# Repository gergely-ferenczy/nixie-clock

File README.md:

4 digit IN-8-2 Nixie clock with schematic and code implementation for a TM4C1231 microcontroller.

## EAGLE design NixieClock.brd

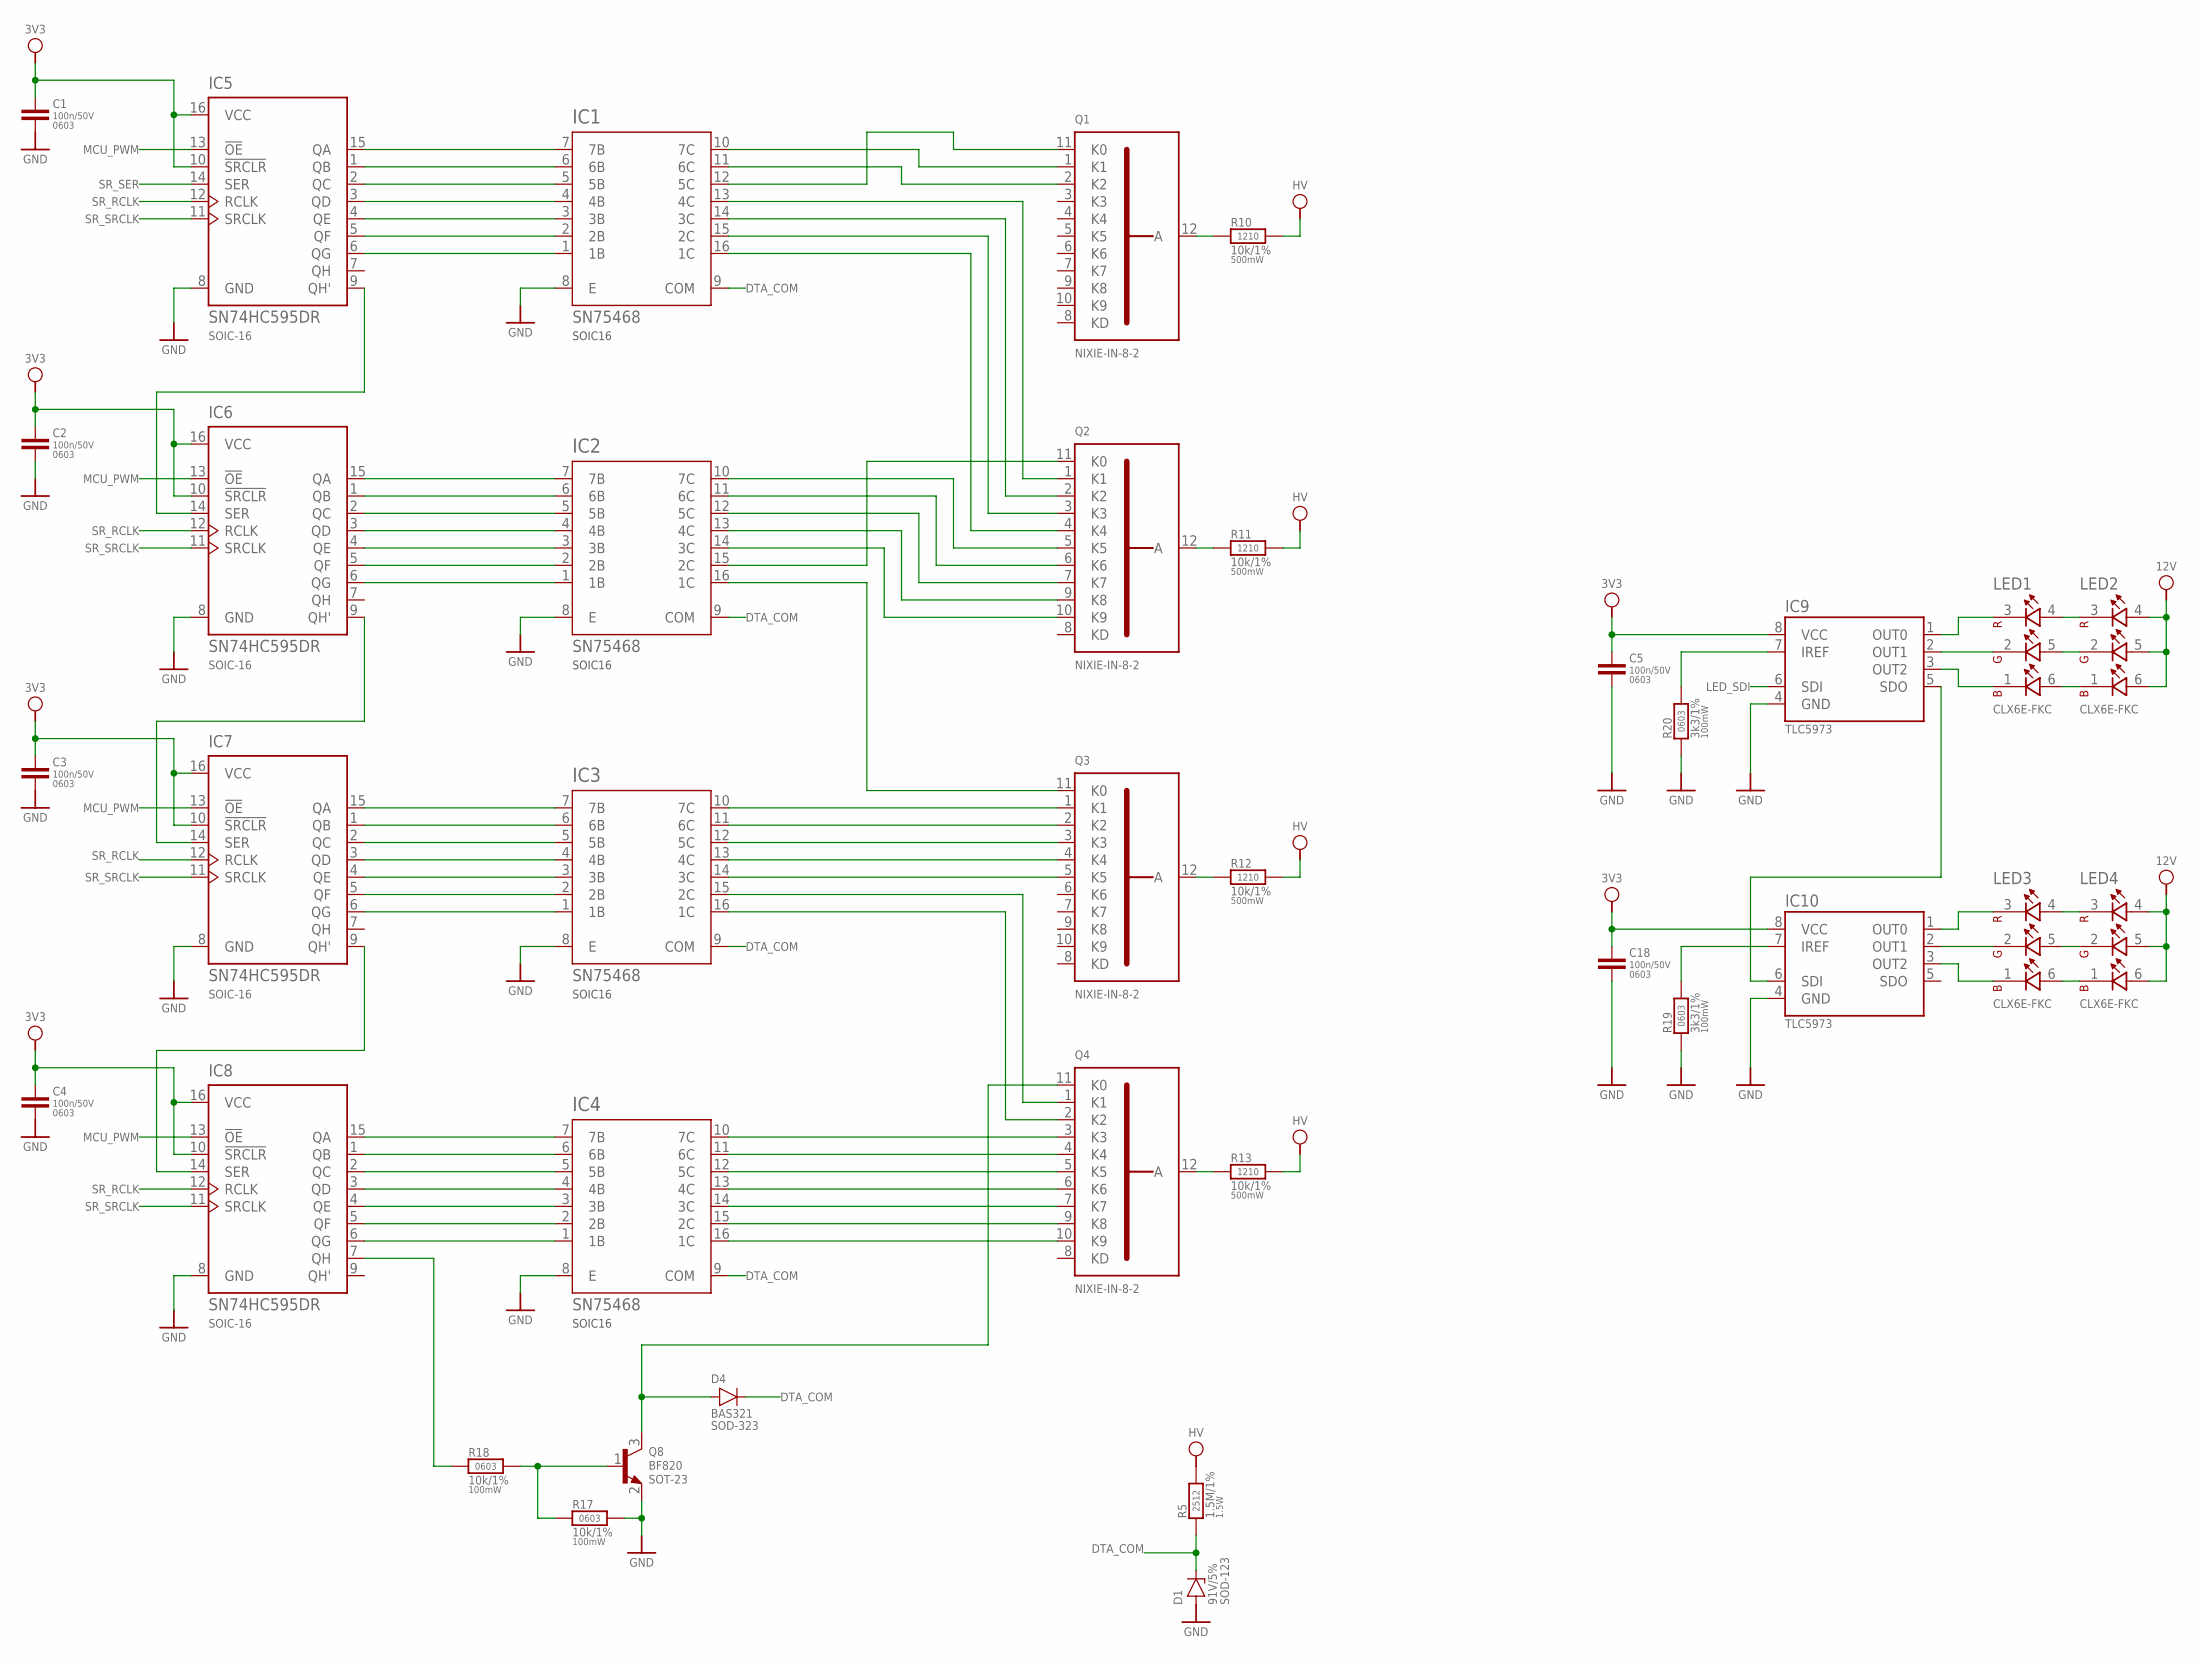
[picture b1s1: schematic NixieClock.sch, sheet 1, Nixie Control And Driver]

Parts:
C1, C2, C3, C4, C5, C18: 100n/50V; CAPC1608X80N
D1: 91V/5%; SOD3716X135N
D4: BAS321; SOD2512X110N
IC1, IC2, IC3, IC4: SN75468; SOIC127P600X175-16N
IC5, IC6, IC7, IC8: SN74HC595DR; SOIC127P600X175-16N
IC9, IC10: TLC5973; SOIC127P600X175-8N
LED1, LED2, LED3, LED4: CLX6E-FKC
Q1, Q2, Q3, Q4: NIXIE-IN-8-2
Q8: BF820; SOT95P230X110-3N
R5: 1.5M/1%; RESC6331X65N
R10, R11, R12, R13: 10k/1%; RESC3225X60N
R17, R18: 10k/1%; RESC1608X50N
R19, R20: 3k3/1%; RESC1608X50N

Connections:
3V3: C1.1, C2.1, C3.1, C4.1, C5.1, C18.1, IC5.10 (!SRCLR), IC5.16 (VCC), IC6.10 (!SRCLR), IC6.16 (VCC), IC7.10 (!SRCLR), IC7.16 (VCC), IC8.10 (!SRCLR), IC8.16 (VCC), IC9.8 (VCC), IC10.8 (VCC); also elsewhere on the board
12V: LED2.4 (ARED), LED2.5 (AGREEN), LED2.6 (ABLUE), LED4.4 (ARED), LED4.5 (AGREEN), LED4.6 (ABLUE); also elsewhere on the board
DTA_COM: D1.1, D4.1, IC1.9 (COM), IC2.9 (COM), IC3.9 (COM), IC4.9 (COM), R5.1
GND: C1.2, C2.2, C3.2, C4.2, C5.2, C18.2, D1.2, IC1.8 (E), IC2.8 (E), IC3.8 (E), IC4.8 (E), IC5.8 (GND), IC6.8 (GND), IC7.8 (GND), IC8.8 (GND), IC9.4 (GND), IC10.4 (GND), Q8.2 (E), R17.2, R19.1, R20.1; also elsewhere on the board
HV: R5.2, R10.2, R11.2, R12.2, R13.2; also elsewhere on the board
LED_SDI: IC9.6 (SDI); also elsewhere on the board
MCU_PWM: IC5.13 (!OE), IC6.13 (!OE), IC7.13 (!OE), IC8.13 (!OE); also elsewhere on the board
unnamed: IC1.7 (7B), IC5.15 (QA)
unnamed: IC1.6 (6B), IC5.1 (QB)
unnamed: IC1.5 (5B), IC5.2 (QC)
unnamed: IC1.4 (4B), IC5.3 (QD)
unnamed: IC1.3 (3B), IC5.4 (QE)
unnamed: IC1.2 (2B), IC5.5 (QF)
unnamed: IC1.1 (1B), IC5.6 (QG)
unnamed: IC5.9 (QH'), IC6.14 (SER)
unnamed: IC1.10 (7C), Q1.1 (K1)
unnamed: IC1.11 (6C), Q1.2 (K2)
unnamed: IC1.12 (5C), Q1.11 (K0)
unnamed: IC1.13 (4C), Q2.1 (K1)
unnamed: IC1.14 (3C), Q2.2 (K2)
unnamed: IC1.15 (2C), Q2.3 (K3)
unnamed: IC1.16 (1C), Q2.4 (K4)
unnamed: IC6.9 (QH'), IC7.14 (SER)
unnamed: IC2.10 (7C), Q2.5 (K5)
unnamed: IC2.11 (6C), Q2.6 (K6)
unnamed: IC2.12 (5C), Q2.7 (K7)
unnamed: IC2.13 (4C), Q2.9 (K8)
unnamed: IC2.14 (3C), Q2.10 (K9)
unnamed: IC2.15 (2C), Q2.11 (K0)
unnamed: IC2.7 (7B), IC6.15 (QA)
unnamed: IC7.9 (QH'), IC8.14 (SER)
unnamed: IC2.6 (6B), IC6.1 (QB)
unnamed: IC2.5 (5B), IC6.2 (QC)
unnamed: IC2.4 (4B), IC6.3 (QD)
unnamed: IC2.3 (3B), IC6.4 (QE)
unnamed: IC2.2 (2B), IC6.5 (QF)
unnamed: IC2.1 (1B), IC6.6 (QG)
unnamed: IC3.7 (7B), IC7.15 (QA)
unnamed: IC3.6 (6B), IC7.1 (QB)
unnamed: IC3.5 (5B), IC7.2 (QC)
unnamed: IC3.4 (4B), IC7.3 (QD)
unnamed: IC3.3 (3B), IC7.4 (QE)
unnamed: IC3.2 (2B), IC7.5 (QF)
unnamed: IC3.1 (1B), IC7.6 (QG)
unnamed: IC8.7 (QH), R18.1
unnamed: IC9.1 (OUT0), LED1.3 (CRED)
unnamed: IC9.3 (OUT2), LED1.1 (CBLUE)
unnamed: IC9.2 (OUT1), LED1.2 (CGREEN)
unnamed: IC4.11 (6C), Q4.4 (K4)
unnamed: IC10.1 (OUT0), LED3.3 (CRED)
unnamed: IC4.7 (7B), IC8.15 (QA)
unnamed: IC4.6 (6B), IC8.1 (QB)
unnamed: IC4.5 (5B), IC8.2 (QC)
unnamed: IC4.4 (4B), IC8.3 (QD)
unnamed: IC4.3 (3B), IC8.4 (QE)
unnamed: IC4.2 (2B), IC8.5 (QF)
unnamed: IC4.1 (1B), IC8.6 (QG)
unnamed: IC2.16 (1C), Q3.11 (K0)
unnamed: IC3.14 (3C), Q3.5 (K5)
unnamed: IC3.13 (4C), Q3.4 (K4)
unnamed: IC3.12 (5C), Q3.3 (K3)
unnamed: Q1.12 (A), R10.1
unnamed: IC3.11 (6C), Q3.2 (K2)
unnamed: IC3.10 (7C), Q3.1 (K1)
unnamed: IC3.15 (2C), Q4.1 (K1)
unnamed: IC3.16 (1C), Q4.2 (K2)
unnamed: IC4.10 (7C), Q4.3 (K3)
unnamed: IC4.12 (5C), Q4.5 (K5)
unnamed: IC4.13 (4C), Q4.6 (K6)
unnamed: IC4.14 (3C), Q4.7 (K7)
unnamed: Q8.1 (B), R17.1, R18.2
unnamed: IC4.15 (2C), Q4.9 (K8)
unnamed: IC4.16 (1C), Q4.10 (K9)
unnamed: D4.2, Q4.11 (K0), Q8.3 (C)
unnamed: IC10.2 (OUT1), LED3.2 (CGREEN)
unnamed: IC10.3 (OUT2), LED3.1 (CBLUE)
unnamed: Q2.12 (A), R11.1
unnamed: Q3.12 (A), R12.1
unnamed: Q4.12 (A), R13.1
unnamed: LED3.4 (ARED), LED4.3 (CRED)
unnamed: LED3.5 (AGREEN), LED4.2 (CGREEN)
unnamed: LED3.6 (ABLUE), LED4.1 (CBLUE)
unnamed: LED1.4 (ARED), LED2.3 (CRED)
unnamed: LED1.5 (AGREEN), LED2.2 (CGREEN)
unnamed: LED1.6 (ABLUE), LED2.1 (CBLUE)
unnamed: IC9.7 (IREF), R20.2
unnamed: IC10.7 (IREF), R19.2
unnamed: IC9.5 (SDO), IC10.6 (SDI)
SR_RCLK: IC5.12 (RCLK), IC6.12 (RCLK), IC7.12 (RCLK), IC8.12 (RCLK); also elsewhere on the board
SR_SER: IC5.14 (SER); also elsewhere on the board
SR_SRCLK: IC5.11 (SRCLK), IC6.11 (SRCLK), IC7.11 (SRCLK), IC8.11 (SRCLK); also elsewhere on the board

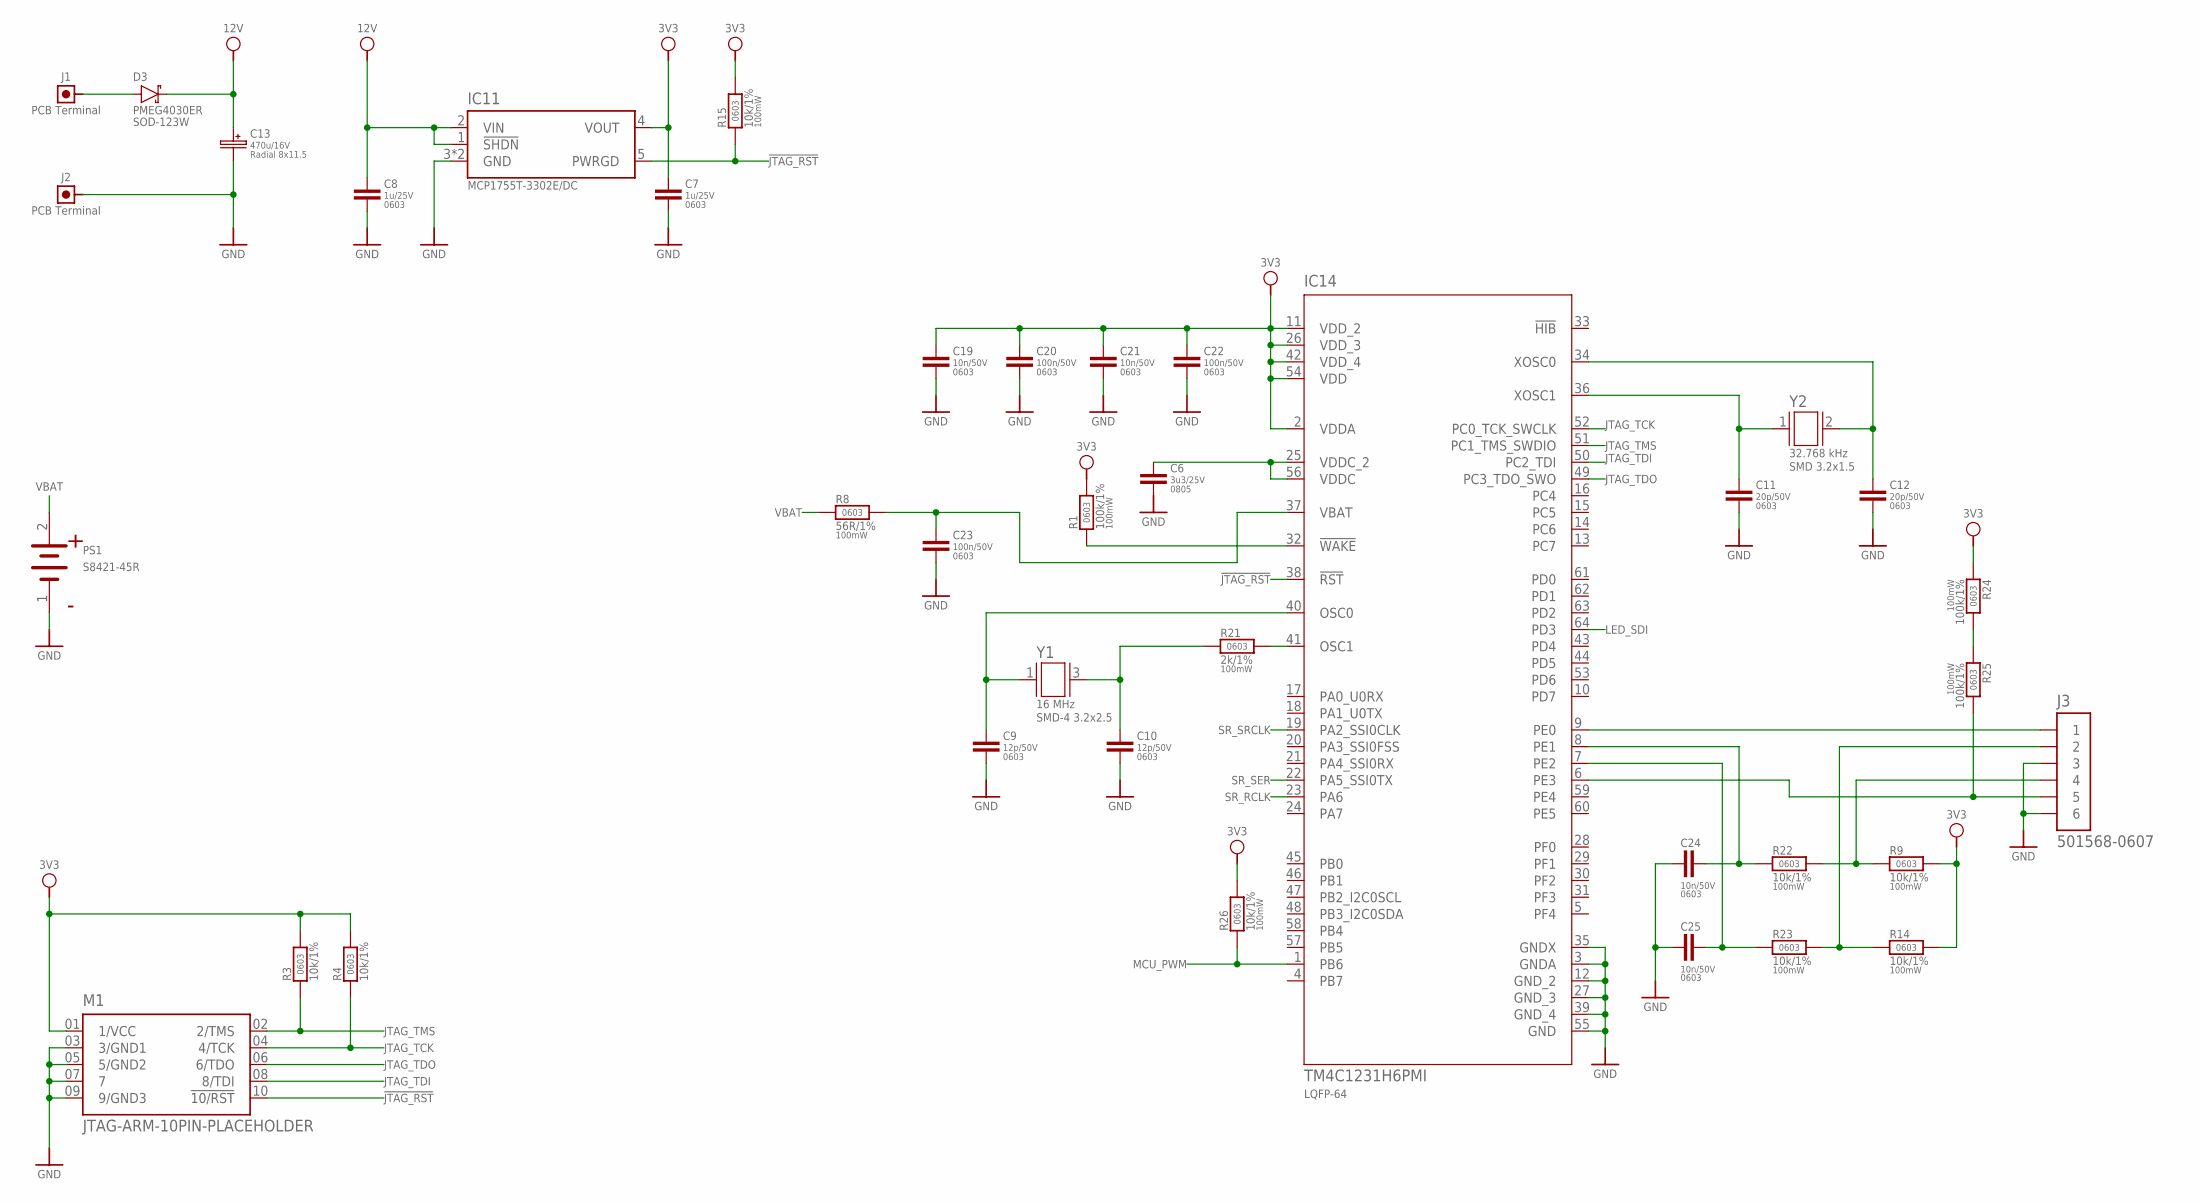
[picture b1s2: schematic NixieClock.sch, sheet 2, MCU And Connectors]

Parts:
C6: 3u3/25V; CAPC2012X145N
C7, C8: 1u/25V; CAPC1608X80N
C9, C10: 12p/50V; CAPC1608X80N
C11, C12: 20p/50V; CAPC1608X80N
C13: 470u/16V; CAPPRD350W60D800H1150B
C19, C21, C24, C25: 10n/50V; CAPC1608X80N
C20, C22, C23: 100n/50V; CAPC1608X80N
D3: PMEG4030ER; SODFL3517X110N
IC11: MCP1755T-3302E/DC; SOT127P700X180-6N
IC14: TM4C1231H6PMI; QFP50P1200X1200X160-64N
J1, J2: PCB Terminal; PCB_TERMINAL_PAD
J3: 501568-0607; MOLEX_501568-0607
M1: JTAG-ARM-10PIN-PLACEHOLDER
PS1: S8421-45R
R1, R24, R25: 100k/1%; RESC1608X50N
R3, R4, R9, R14, R15, R22, R23, R26: 10k/1%; RESC1608X50N
R8: 56R/1%; RESC1608X50N
R21: 2k/1%; RESC1608X50N
Y1: 16 MHz; OSCCC320X250X100N
Y2: 32.768 kHz; OSCCC320X150X90N

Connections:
3V3: C7.1, C19.1, C20.1, C21.1, C22.1, IC11.4 (VOUT), IC14.2 (VDDA), IC14.11 (VDD_2), IC14.26 (VDD_3), IC14.42 (VDD_4), IC14.54 (VDD), M1.01 (1/VCC), R1.2, R3.2, R4.2, R9.2, R14.2, R15.2, R24.1, R26.2; also elsewhere on the board
12V: C8.1, C13.1, D3.1, IC11.1 (!SHDN), IC11.2 (VIN); also elsewhere on the board
!JTAG_RST: IC11.5 (PWRGD), IC14.38 (!RST), M1.10 (!10/RST), R15.1
!WAKE: IC14.32 (!WAKE), R1.1
GND: C6.2, C7.2, C8.2, C9.2, C10.2, C11.2, C12.2, C13.2, C19.2, C20.2, C21.2, C22.2, C23.2, C24.1, C25.1, IC11.3 (GND), IC11.6 (GND), IC14.3 (GNDA), IC14.12 (GND_2), IC14.27 (GND_3), IC14.35 (GNDX), IC14.39 (GND_4), IC14.55 (GND), J2.1, J3.3, J3.6, M1.03 (3/GND1), M1.05 (5/GND2), M1.07 (7), M1.09 (9/GND3), PS1.1 (CATHODE); also elsewhere on the board
JTAG_TCK: IC14.52 (PC0_TCK_SWCLK), M1.04 (4/TCK), R4.1
JTAG_TDI: IC14.50 (PC2_TDI), M1.08 (8/TDI)
JTAG_TDO: IC14.49 (PC3_TDO_SWO), M1.06 (6/TDO)
JTAG_TMS: IC14.51 (PC1_TMS_SWDIO), M1.02 (2/TMS), R3.1
LED_SDI: IC14.64 (PD3); also elsewhere on the board
MCU_LS: IC14.6 (PE3), J3.5, R25.2
MCU_PWM: IC14.1 (PB6), R26.1; also elsewhere on the board
MCU_QEA: C24.2, IC14.8 (PE1), R22.1
MCU_QEB: C25.2, IC14.7 (PE2), R23.1
MCU_SW: IC14.9 (PE0), J3.1
MCU_VBAT: C23.1, IC14.37 (VBAT), R8.2
MCU_VDDC: C6.1, IC14.25 (VDDC_2), IC14.56 (VDDC)
unnamed: R24.2, R25.1
unnamed: IC14.41 (OSC1), R21.2
OSC0: C9.1, IC14.40 (OSC0), Y1.1
OSC1: C10.1, R21.1, Y1.3 (2)
QEA_RAW: J3.4, R9.1, R22.2
QEB_RAW: J3.2, R14.1, R23.2
SR_RCLK: IC14.23 (PA6); also elsewhere on the board
SR_SER: IC14.22 (PA5_SSI0TX); also elsewhere on the board
SR_SRCLK: IC14.19 (PA2_SSI0CLK); also elsewhere on the board
VBAT: PS1.2 (ANODE), R8.1
VSUPP: D3.2, J1.1
XOSC0: C12.1, IC14.34 (XOSC0), Y2.2
XOSC1: C11.1, IC14.36 (XOSC1), Y2.1

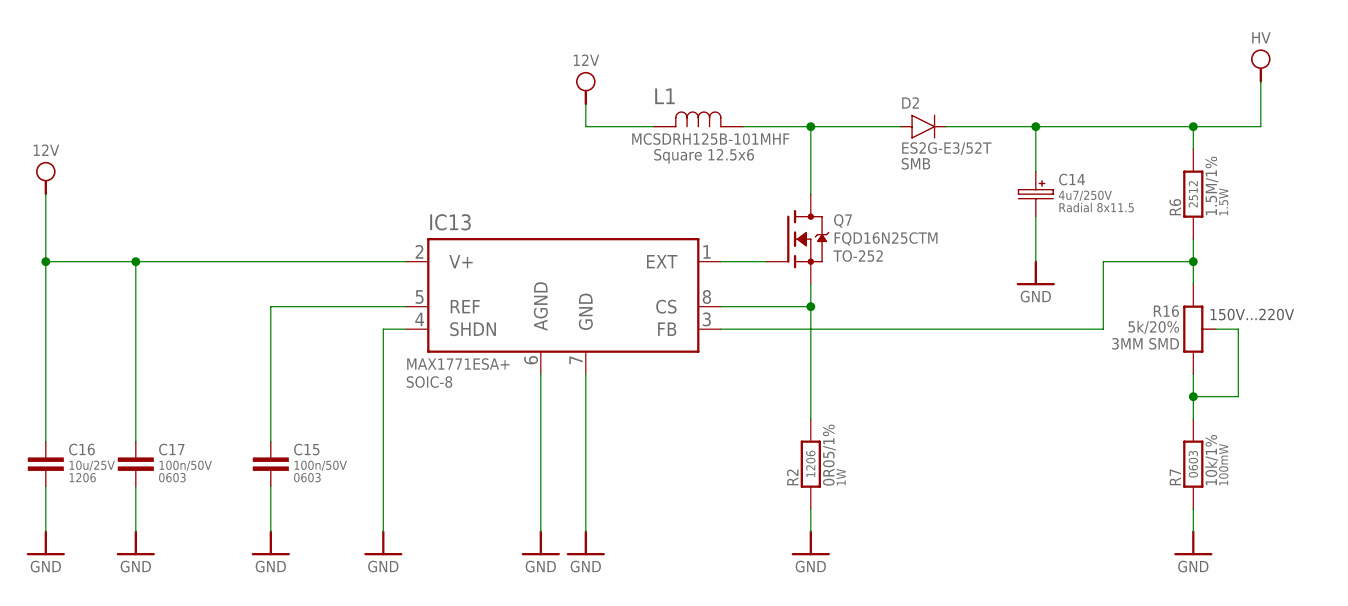
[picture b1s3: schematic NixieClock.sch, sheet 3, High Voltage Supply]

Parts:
C14: 4u7/250V; CAPPRD350W60D800H1150B
C15, C17: 100n/50V; CAPC1608X80N
C16: 10u/25V; CAPC3216X170N
D2: ES2G-E3/52T; DIOM5436X245N
IC13: MAX1771ESA+; SOIC127P600X175-8N
L1: MCSDRH125B-101MHF; INDM120120X600N
Q7: FQD16N25CTM; TO230P990X240-3N
R2: 0R05/1%; RESC3216X70N
R6: 1.5M/1%; RESC6331X65N
R7: 10k/1%; RESC1608X50N
R16: 5k/20%; 22A

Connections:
12V: C16.1, C17.1, IC13.2 (V+), L1.1; also elsewhere on the board
CS: IC13.8 (CS), Q7.3 (S), R2.2
FB: IC13.3 (FB), R6.1, R16.P$1 (1)
GND: C14.2, C15.2, C16.2, C17.2, IC13.4 (SHDN), IC13.6 (AGND), IC13.7 (GND), R2.1, R7.1; also elsewhere on the board
HV: C14.1, D2.1, R6.2; also elsewhere on the board
unnamed: IC13.1 (EXT), Q7.1 (G)
unnamed: R7.2, R16.P$2 (2), R16.P$3 (3)
REF: C15.1, IC13.5 (REF)
SW: D2.2, L1.2, Q7.4 (D)

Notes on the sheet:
150V...220V

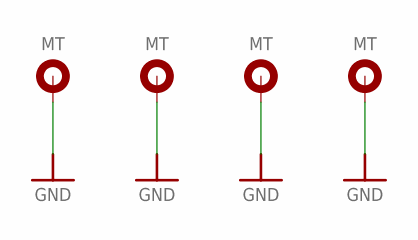
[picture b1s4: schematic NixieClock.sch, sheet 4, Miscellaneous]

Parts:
MT1, MT2, MT3, MT4: MOUNTING_HOLE_3MM

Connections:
GND: MT1.0, MT1.1, MT1.2, MT1.3, MT1.4, MT1.5, MT1.6, MT1.7, MT1.8, MT2.0, MT2.1, MT2.2, MT2.3, MT2.4, MT2.5, MT2.6, MT2.7, MT2.8, MT3.0, MT3.1, MT3.2, MT3.3, MT3.4, MT3.5, MT3.6, MT3.7, MT3.8, MT4.0, MT4.1, MT4.2, MT4.3, MT4.4, MT4.5, MT4.6, MT4.7, MT4.8; also elsewhere on the board

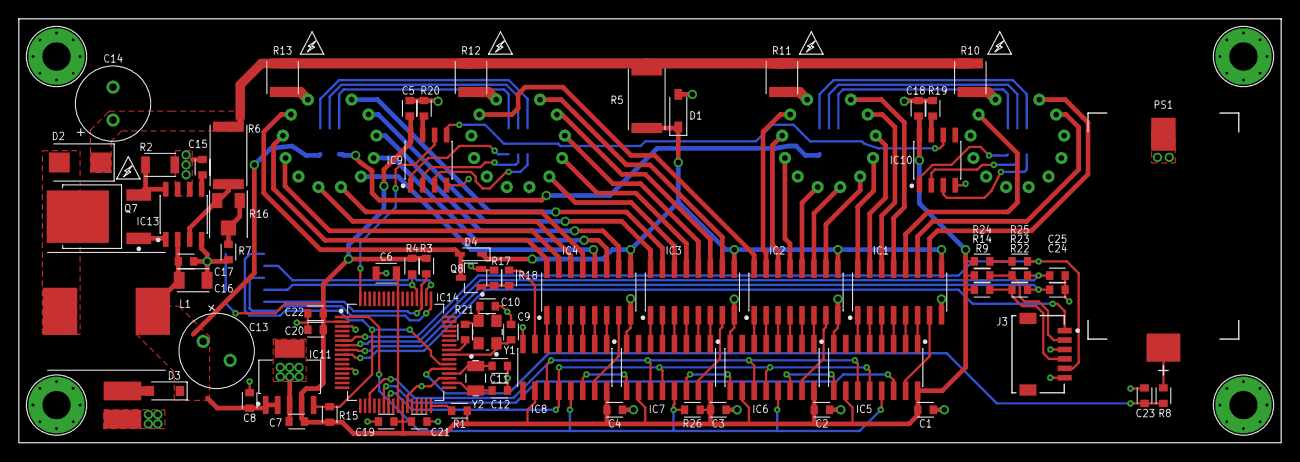
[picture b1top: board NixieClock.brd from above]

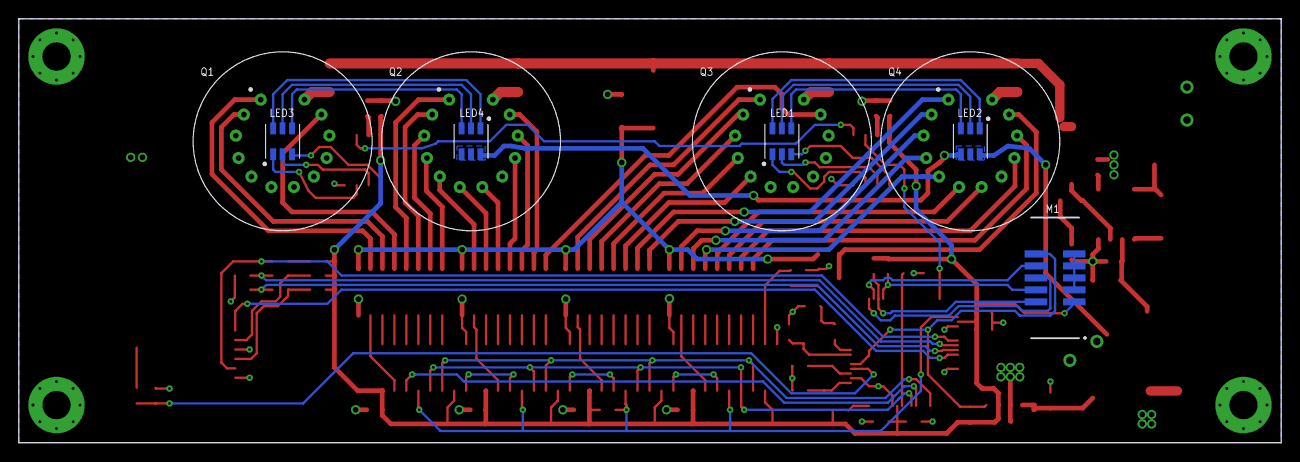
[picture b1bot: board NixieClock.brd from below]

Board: 2 copper layers, 134.0 x 45.0 mm, 90 parts (9 on the bottom side), 119 nets.

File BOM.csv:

"Qty";"Value";"Device";"Package";"Parts";"Description";"MANUFACTURER";"PACKAGE";"PARAMETER";"PARTNUMBER";"VALUE";
"1";"0R05/1%";"ERJ8CWFR050V";"RESC3216X70N";"R2";"SMD Current Sense Resistor, 0R05/1%, 1 W, 1206 [3216], Panasonic";"Panasonic";"1206";"1W";"ERJ8CWFR050V";"0R05/1%";
"2";"1.5M/1%";"MCPWR12FTEA1504";"RESC6331X65N";"R5, R6";"SMT Resistor, 1.5M, 1%, 1.5W, 2512 [6432], MULTICOMP PRO";"MULTICOMP PRO";"2512";"1.5W";"MCPWR12FTEA1504";"1.5M/1%";
"3";"100k/1%";"CRCW0603100KFKEA";"RESC1608X50N";"R1, R24, R25";"SMT Resistor, 100k/1%, 100mW, 0603, VISHAY";"VISHAY";"0603";"100mW";"CRCW0603100KFKEA";"100k/1%";
"11";"100n/50V";"C0603C104M5RACTU";"CAPC1608X80N";"C1, C2, C3, C4, C5, C15, C17, C18, C20, C22, C23";"SMT Capacitor, 100n/50V, X7R, 10%, 0603, KEMET";"KEMET";"0603";"X7R, 20%";"C0603C104M5RACTU";"100n/50V";
"11";"10k/1%";"CRCW060310K0FKEA";"RESC1608X50N";"R3, R4, R7, R9, R14, R15, R17, R18, R22, R23, R26";"SMT Resistor, 10k/1%, 100mW, 0603, VISHAY";"VISHAY";"0603";"100mW";"CRCW060310K0FKEA";"10k/1%";
"4";"10k/1%";"CRCW121010K0FKEA";"RESC3225X60N";"R10, R11, R12, R13";"SMT Resistor, 10k/1%, 500mW, 1210, VISHAY";"VISHAY";"1210";"500mW";"CRCW121010K0FKEA";"10k/1%";
"4";"10n/50V";"C0603C103K5RACTU";"CAPC1608X80N";"C19, C21, C24, C25";"SMT Capacitor, 10n/50V, X7R, 10%, 0603, KEMET";"KEMET";"0603";"X7R, 10%";"C0603C103K5RACTU";"10n/50V";
"1";"10u/25V";"C1206C106K3PACTU";"CAPC3216X170N";"C16";"SMT Capacitor, 10u/25V, X5R, ±10%, 1206, KEMET";"KEMET";"1206";"X5R";"C1206C106K3PACTU";"10u/25V";
"2";"12p/50V";"C0603C120J5GACTU";"CAPC1608X80N";"C9, C10";"SMT Capacitor, 12p/50V, C0G/NP0, ±5%, 0603, KEMET";"KEMET";"0603";"C0G/NP0, ±5%";"C0603C120J5GACTU";"12p/50V";
"1";"16 MHz";"MCSJK-7U-16.00-10-10-80-B-10";"OSCCC320X250X100N";"Y1";"SMT Crystal, 16 MHz, SMD, 3.2mm x 2.5mm, 10 ppm, 10 pF, 10 ppm";"ABRACON";"SMD-4 3.2x2.5";"±10ppm, 10pF";"MCSJK-7U-16.00-10-10-80-B-10";"16 MHz";
"2";"1u/25V";"CL10A105KA8NNNC";"CAPC1608X80N";"C7, C8";"SMT Capacitor, 1u/25V, X7R, 10%, 0603, SAMSUNG ELECTRO-MECHANICS";"SAMSUNG ELECTRO-MECHANICS";"0603";"X7R, 10%";"CL10A105KA8NNNC";"1u/25V";
"2";"20p/50V";"C0603C200J1GACTU";"CAPC1608X80N";"C11, C12";"SMT Capacitor, 20p/50V, C0G/NP0, ±5%, 0603, KEMET";"KEMET";"0603";"C0G/NP0, ±5%";"C0603C200J1GACTU";"20p/50V";
"1";"2k/1%";"CRCW06032K00FKEA";"RESC1608X50N";"R21";"SMT Resistor, 2k/1%, 100mW, 0603, VISHAY";"VISHAY";"0603";"100mW";"CRCW06032K00FKEA";"2k/1%";
"1";"32.768 kHz";"ABS07AIG-32.768KHZ-1-T";"OSCCC320X150X90N";"Y2";"SMT Crystal, 32.768 kHz, SMD, 3.2mm x 1.5mm, 12.5 pF, 10 ppm";"ABRACON";"SMD 3.2x1.5";"±10 ppm, 12.5 pF";"ABS07AIG-32.768KHZ-1-T";"32.768 kHz";
"2";"3k3/1%";"MCWR06X3301FTL";"RESC1608X50N";"R19, R20";"SMT Resistor, 3k3/1%, 100mW, 0603, MULTICOMP PRO";"MULTICOMP PRO";"0603";"100mW";"MCWR06X3301FTL";"3k3/1%";
"1";"3u3/25V";"C2012X7R1E335K125";"CAPC2012X145N";"C6";"SMT Capacitor, 3u3/25V, X7R, 10%, 0805, TDK";"TDK";"0805";"X7R, 10%";"C2012X7R1E335K125AB";"3u3/25V";
"1";"470u/16V";"ECA1CM471";"CAPPRD350W60D800H1150B";"C13";"Electrolytic Capacitor, 470 µF, 16 V, ± 20%, Radial Leaded, Panasonic";"Panasonic";"Radial 8x11.5";"Alu, 20%";"ECA1CM471";"470u/16V";
"1";"4u7/250V";"ECA2EHG4R7";"CAPPRD350W60D800H1150B";"C14";"Electrolytic Capacitor, 4.7 µF, 250 V, ± 20%, Radial Leaded, Panasonic";"Panasonic";"Radial 8x11.5";"Alu, 20%";"ECA2EHG4R7";"4u7/250V";
"1";"501568-0607";"MOLEX_501568-0607";"MOLEX_501568-0607";"J3";"PCB Header, 1.00mm Pitch, Pico-Clasp, Single Row, Right-Angle, Surface Mount, Tin Plated, with Inner Positive Lock, 6 Circuits";"MOLEX";"";"";"501568-0607";"501568-0607";
"1";"56R/1%";"CRCW060356R0FKEA";"RESC1608X50N";"R8";"SMT Resistor, 56R/1%, 100mW, 0603, VISHAY";"VISHAY";"0603";"100mW";"CRCW060333R0FKEA";"56R/1%";
"1";"5k/20%";"22AR5K";"22A";"R16";"Trimpot, Single Turn, Cermet, Top Adjust, 5 kohm, Surface Mount, 1 Turns";"TT ELECTRONICS / BI TECHNOL";"3MM SMD";"";"";"5k/20%";
"1";"91V/5%";"MMSZ5270BT1G";"SOD3716X135N";"D1";"Zener Diode, Voltage Regulator, 91 V, 500 mW, 5 %, SOD-123, ON Semiconductor";"ON Semiconductor";"SOD-123";"500mW";"MMSZ5270BT1G";"91V/5%";
"1";"BAS321";"BAS321";"SOD2512X110N";"D4";"Small Signal Diode, 250 V, 250 mA, 1.25 V, 50 ns, 9 A";"NEXPERIA";"SOD-323";"250V, 250mA";"BAS321/8F";"BAS321";
"1";"BF820";"BF820";"SOT95P230X110-3N";"Q8";"NPN Transistor, Bipolar (BJT), 300 V, 50 mA, 250 mW, SOT-23, NEXPERIA";"NEXPERIA";"SOT-23";"";"BF820";"";
"4";"CLX6E-FKC";"CLX6E-FKC";"CLX6E-FKC";"LED1, LED2, LED3, LED4";"LED, Red, Green, Blue, SMD, Square, R 15mA, G 10mA, B 10mA, CREE";"CREE";"SMD 3.5x3.4x2.8 mm";"";"CLX6E-FKC-CH1M1D1BB7C3D3";"CLX6E-FKC";
"1";"ES2G-E3/52T";"ES2G-E3/52T";"DIOM5436X245N";"D2";"Fast / Ultrafast Diode, 400 V, 2 A, 900 mV, 35 ns, 50 A, SMB, VISHAY";"VISHAY";"SMB";"400V/2A";"ES2G-E3/52T";"ES2G-E3/52T";
"1";"FQD16N25CTM";"FQD16N25CTM";"TO230P990X240-3N";"Q7";"Power MOSFET, N Channel, 250 V, 16 A, 0.22 ohm, TO-252 (DPAK), Surface Mount";"ON Semiconductor";"TO-252";"";"FQD16N25CTM";"";
"1";"JTAG-ARM-10PIN-PLACEHOLDER";"JTAG-ARM-10PIN-PLACEHOLDER";"JTAG-ARM-10PIN-PLACEHOLDER";"M1";"JTAG 10-pin ARM compatible connector placeholder.";"";"";"";"";"";
"1";"MAX1771ESA+";"MAX1771ESA+";"SOIC127P600X175-8N";"IC13";"DC/DC Controller, Boost (Step Up), 3 V to 16.5 V, 1 Output, 300 kHz, SOIC-8";"Maxim Integrated";"SOIC-8";"";"MAX1771ESA+";"";
"1";"MCP1755T-3302E/DC";"MCP1755T-3302E/DC";"SOT127P700X180-6N";"IC11";"Fixed LDO Voltage Regulator, 3.6V to 16V, 300mV Dropout, 3.3Vout, 300mAout, SOT-223-5, MICROCHIP";"MICROCHIP";"SOT-223-5";"";"MCP1755T-3302E/DC";"";
"1";"MCSDRH125B-101MHF";"MCSDRH125B-101MHF";"INDM120120X600N";"L1";"Power Inductor (SMD), 100 µH, 2.4 A, Shielded, 2.2 A, MCSDRH125B Series, 12.5mm x 12.5mm x 6mm";"Multicomp PRO";"Square 12.5x6";"";"MCSDRH125B-101MHF";"";
"4";"MOUNTING_HOLE_3MM";"MOUNTING_HOLE_3MM";"MOUNTING_HOLE_3MM";"MT1, MT2, MT3, MT4";"";"";"";"";"";"";
"4";"NIXIE-IN-8-2";"NIXIE-IN-8-2";"NIXIE-IN-8-2";"Q1, Q2, Q3, Q4";"";"";"";"";"";"";
"2";"PCB Terminal";"PCB_TERMINAL_PAD";"PCB_TERMINAL_PAD";"J1, J2";"";"";"";"4mmx2mm";"";"PCB Terminal";
"1";"PMEG4030ER";"PMEG4010CEJ";"SODFL3517X110N";"D3";"Schottky Rectifier, 40 V, 3 A, 540 mV, SOD-123W, NEXPERIA";"NEXPERIA";"SOD-123W";"40V, 3A";"PMEG4030ER,115";"PMEG4030ER";
"1";"S8421-45R";"S8421-45R";"S8421-45R";"PS1";"Battery Holder (Open) Coin, 20.0mm 1 Cell SMD (SMT) Tab";"Harwin";"";"";"S8421-45R";"S8421-45R";
"4";"SN74HC595DR";"SN74HC595DR";"SOIC127P600X175-16N";"IC5, IC6, IC7, IC8";"8-Bit Shift Register With 3-State Outputs";"Texas Instruments";"SOIC-16";"";"SN74HC595DR";"";
"4";"SN75468";"SN75468";"SOIC127P600X175-16N";"IC1, IC2, IC3, IC4";"100-V, 7-ch darlington array with TTL or CMOS compatibility";"Texas Instruments";"SOIC16";"";"SN75468D";"";
"2";"TLC5973";"TLC5973";"SOIC127P600X175-8N";"IC9, IC10";"LED Driver, 3-Channel, 12-Bit, PWM Constant-Current with Single-Wire Interface, Texas Instruments";"Texas Instruments";"SOIC-8";"";"TLC5973";"TLC5973";
"1";"TM4C1231H6PMI";"TM4C1231H6PMI";"QFP50P1200X1200X160-64N";"IC14";"";"Texas Instruments";"LQFP-64";"";"TM4C1231H6PMI";"";

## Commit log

2020-12-13 Added selectable pdf.
